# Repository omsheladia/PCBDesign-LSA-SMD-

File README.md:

# PCBDesign-LSA
  Behind the Designing of the Line Sensing Array(L.S.A)

## Using kiCAD - Open Source Software
This repository contains hardware design files and datasheets for the Line Sensor Array. This project is still in development and is not ready for release yet.
Coming soon with a finalised touch.

## Features
* Components can be proctured easily.
* Easy connections for output signals.
* Compact enough to fit into any project.
* Distinguished trace widths for Signal and Power Routes.
 
## Uses
* Obstacle detection on a clear path.
* Line Following.
* Distinguish Colours on a path.

## Components Used
Component | Description
--------- | -----------
LM324 I.C. | Op-Amp I.C.
Photodiode | Absorb light
Resistor | Limit Current
LED | Emit Light
FRC Connector | Connect PCB with other circuits
14 Pin I.C. Socket | Plug LM324 I.C.
  
## Tools:
To view/modify the files from this repository, install KiCAD from: https://kicad.org

## Layout

## Plots

### Front View 

### Back View

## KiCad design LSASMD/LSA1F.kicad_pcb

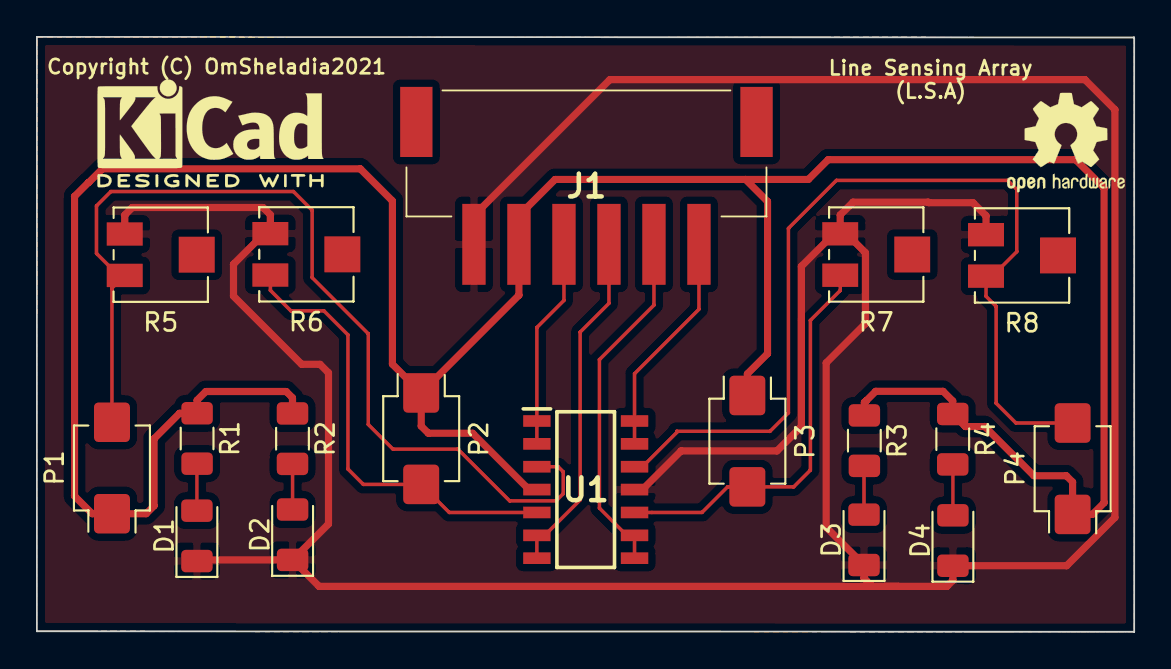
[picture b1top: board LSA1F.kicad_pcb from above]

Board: 2 copper layers, 61.0 x 33.0 mm, 18 parts (0 on the bottom side), 14 nets.

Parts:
D1, D2, D3, D4: LED; LED_1206_3216Metric
J1: S6B-XH-SM4-TB__LF__SN_; S6BXHSM4TBLFSN
P1, P2, P3, P4: D_Photo; Osram_SMD-DIL2_4.5x4.0mm
R1, R2, R3, R4: R_US; R_1206_3216Metric
R5, R6, R7, R8: R_POT_Small; Potentiometer_Vishay_TS53YJ_Vertical
U1: LM324N_NOPB; SOIC127P600X175-14N

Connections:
01: J1.3, U1.1, U1.2
02: J1.4, U1.6, U1.7
03: J1.5, U1.8, U1.9
04: J1.6, U1.13, U1.14
A1: P1.2, R5.1, U1.3
A2: P2.2, R6.1, U1.5
A3: P3.2, R7.1, U1.10
A4: P4.2, R8.1, U1.12
GND: D1.1, D2.1, D3.1, D4.1, J1.1, R5.3, R6.3, R7.3, R8.3, U1.11
unnamed: D1.2, R1.2
unnamed: D2.2, R2.2
unnamed: D3.2, R3.2
unnamed: D4.2, R4.2
VCC: J1.2, P1.1, P2.1, P3.1, P4.1, R1.1, R2.1, R3.1, R4.1, U1.4

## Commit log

2021-08-03 Resources Added
2021-08-03 Updated resources
2021-09-17 3D image changed
2021-10-24 Changed F.Cu Colour

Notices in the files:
LSASMD/LSA1F.kicad_pcb:
Copyright (C) OmSheladia2021
